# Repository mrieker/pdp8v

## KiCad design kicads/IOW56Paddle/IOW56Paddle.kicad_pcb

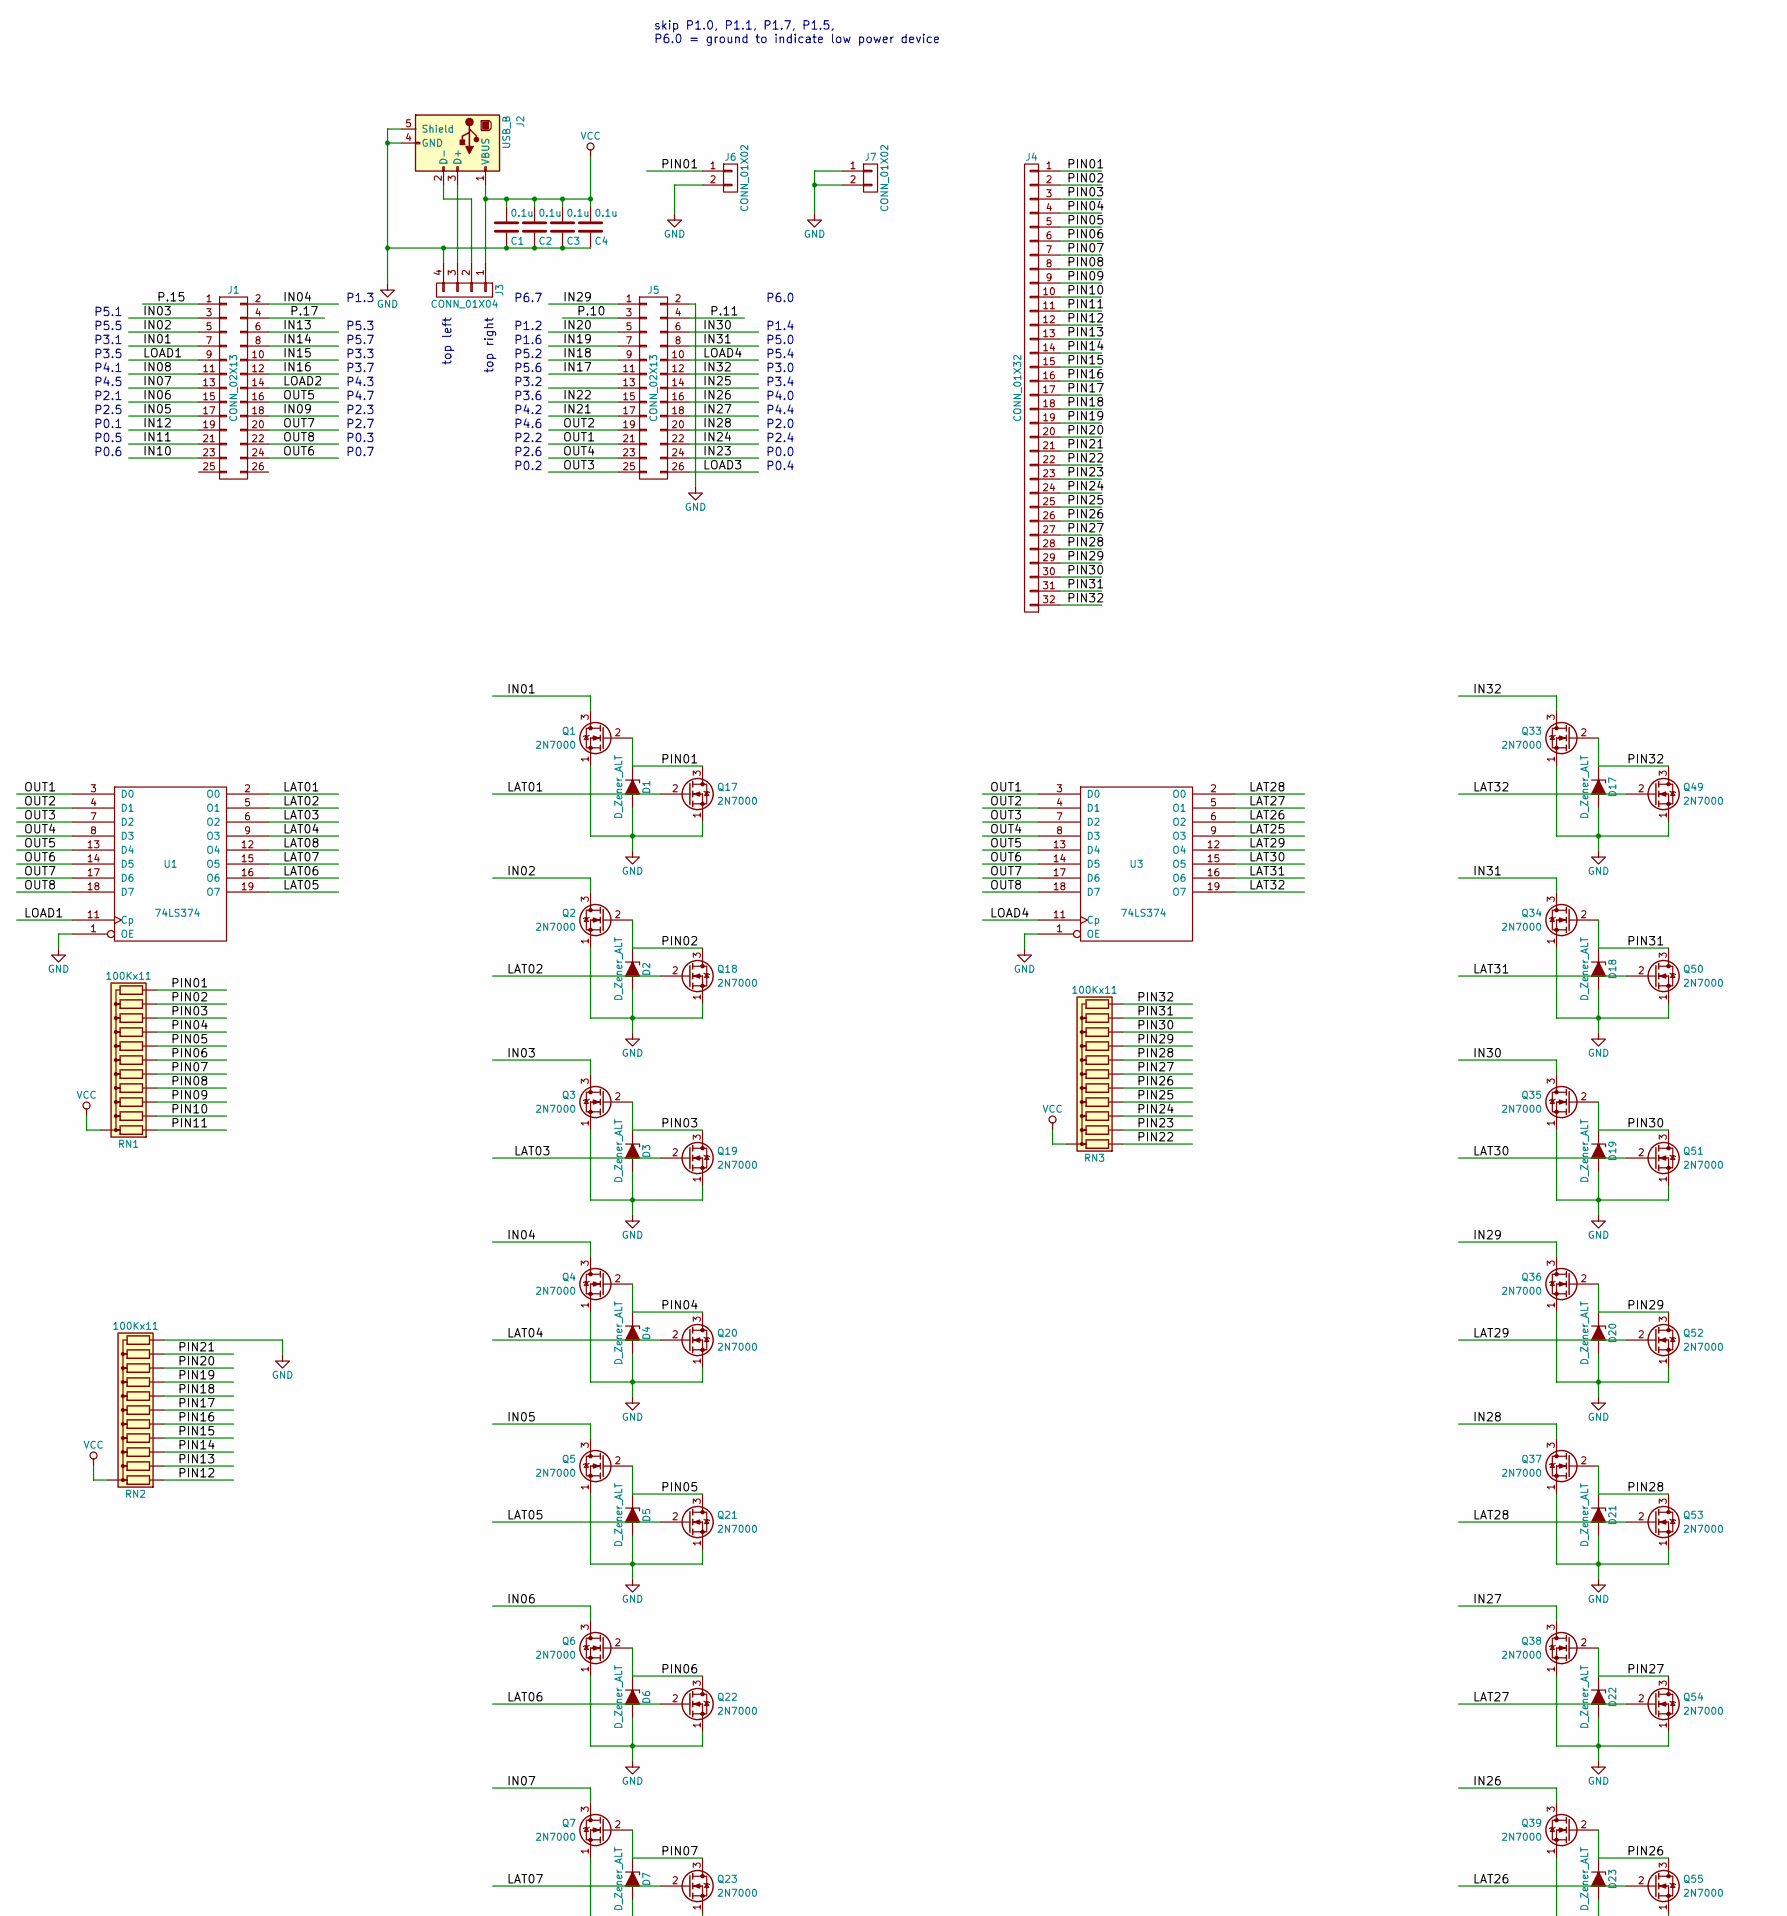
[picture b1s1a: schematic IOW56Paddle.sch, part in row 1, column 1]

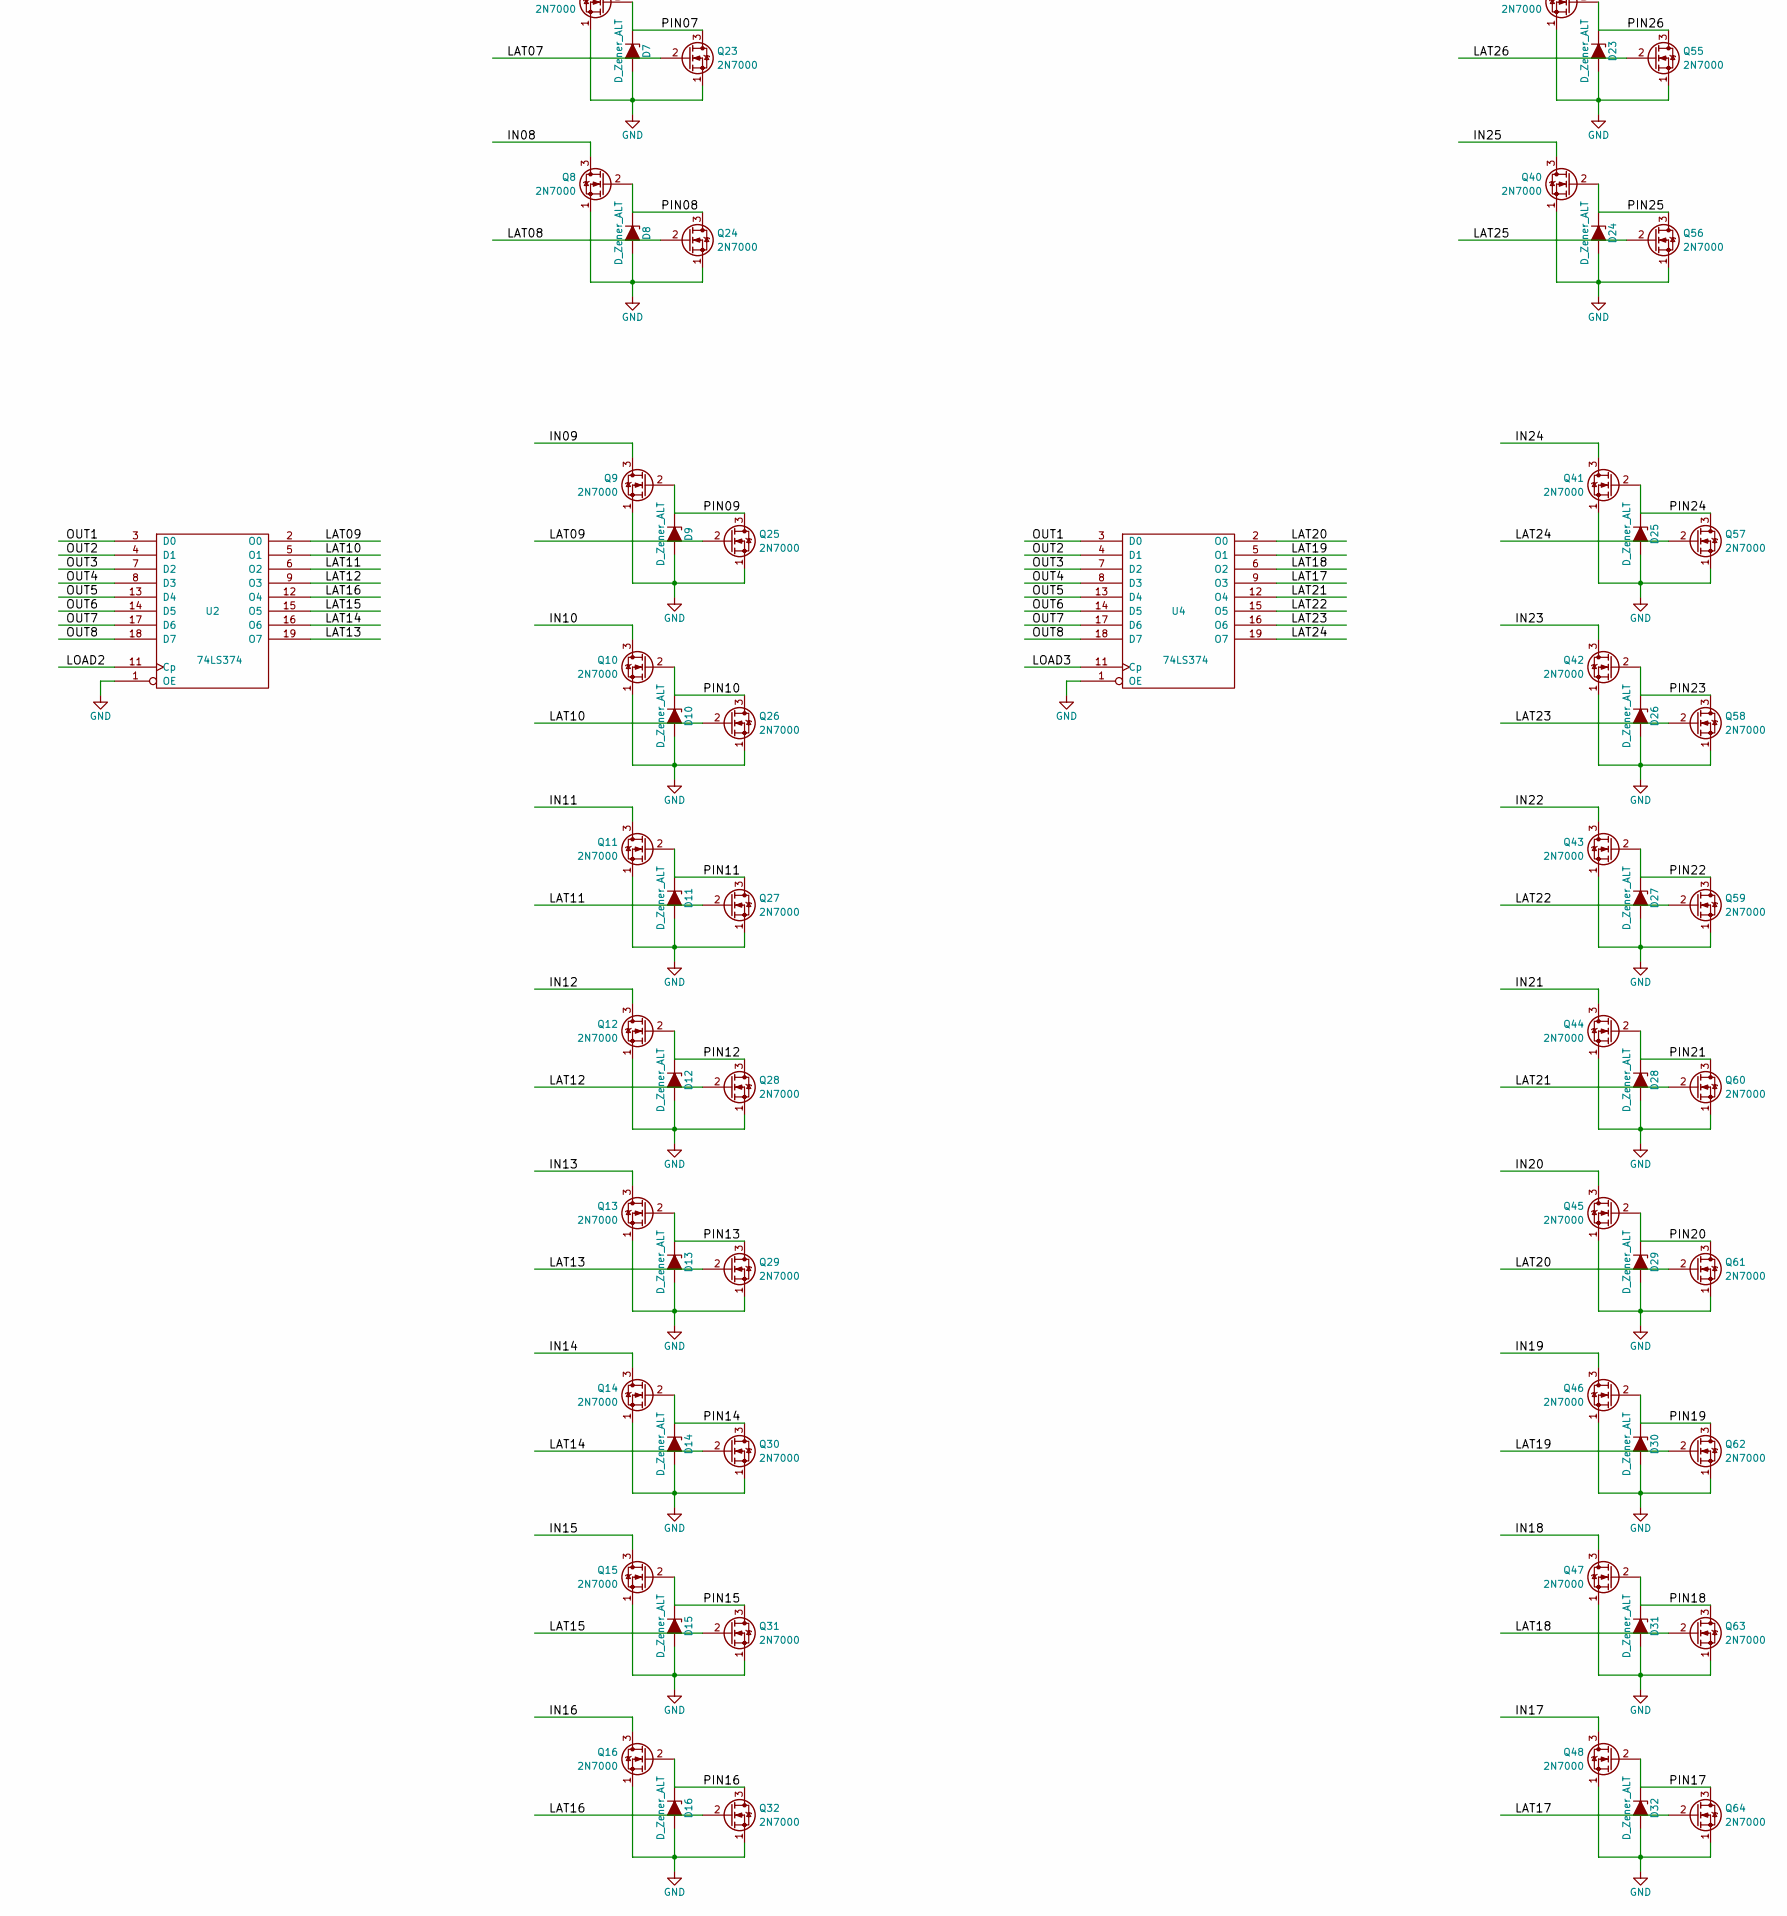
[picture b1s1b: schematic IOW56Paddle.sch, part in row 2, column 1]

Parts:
C1, C2, C3, C4: 0.1u; C_Axial_L5.1mm_D3.1mm_P7.50mm_Horizontal
D1, D2, D3, D4, D5, D6, D7, D8, D9, D10, D11, D12, D13, D14, D15, D16, D17, D18, D19, D20, D21, D22, D23, D24, D25, D26, D27, D28, D29, D30, D31, D32: D_Zener_ALT; D_DO-35_SOD27_P6.35mm_Horizontal
J1, J5: CONN_02X13; Pin_Header_Straight_2x13_Pitch2.54mm
J2: USB_B
J3: CONN_01X04; Pin_Header_Straight_1x04_Pitch2.54mm
J4: CONN_01X32; Pin_Header_Straight_1x32_Pitch2.54mm
J6, J7: CONN_01X02; Pin_Header_Straight_1x02_Pitch2.54mm
Q1, Q2, Q3, Q4, Q5, Q6, Q7, Q8, Q9, Q10, Q11, Q12, Q13, Q14, Q15, Q16, Q17, Q18, Q19, Q20, Q21, Q22, Q23, Q24, Q25, Q26, Q27, Q28, Q29, Q30, Q31, Q32, Q33, Q34, Q35, Q36, Q37, Q38, Q39, Q40, Q41, Q42, Q43, Q44, Q45, Q46, Q47, Q48, Q49, Q50, Q51, Q52, Q53, Q54, Q55, Q56, Q57, Q58, Q59, Q60, Q61, Q62, Q63, Q64: 2N7000; TO-92_Molded_Wide
RN1, RN2, RN3: 100Kx11; R_Array_SIP12
U1, U2, U3, U4: 74LS374; DIP-20_W7.62mm

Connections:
/IN01: J1.7, Q1.3 (D)
/IN02: J1.5, Q2.3 (D)
/IN03: J1.3, Q3.3 (D)
/IN04: J1.2, Q4.3 (D)
/IN05: J1.17, Q5.3 (D)
/IN06: J1.15, Q6.3 (D)
/IN07: J1.13, Q7.3 (D)
/IN08: J1.11, Q8.3 (D)
/IN09: J1.18, Q9.3 (D)
/IN10: J1.23, Q10.3 (D)
/IN11: J1.21, Q11.3 (D)
/IN12: J1.19, Q12.3 (D)
/IN13: J1.6, Q13.3 (D)
/IN14: J1.8, Q14.3 (D)
/IN15: J1.10, Q15.3 (D)
/IN16: J1.12, Q16.3 (D)
/IN17: J5.11, Q48.3 (D)
/IN18: J5.9, Q47.3 (D)
/IN19: J5.7, Q46.3 (D)
/IN20: J5.5, Q45.3 (D)
/IN21: J5.17, Q44.3 (D)
/IN22: J5.15, Q43.3 (D)
/IN23: J5.24, Q42.3 (D)
/IN24: J5.22, Q41.3 (D)
/IN25: J5.14, Q40.3 (D)
/IN26: J5.16, Q39.3 (D)
/IN27: J5.18, Q38.3 (D)
/IN28: J5.20, Q37.3 (D)
/IN29: J5.1, Q36.3 (D)
/IN30: J5.6, Q35.3 (D)
/IN31: J5.8, Q34.3 (D)
/IN32: J5.12, Q33.3 (D)
/LAT01: Q17.2 (G), U1.2 (O0)
/LAT02: Q18.2 (G), U1.5 (O1)
/LAT03: Q19.2 (G), U1.6 (O2)
/LAT04: Q20.2 (G), U1.9 (O3)
/LAT05: Q21.2 (G), U1.19 (O7)
/LAT06: Q22.2 (G), U1.16 (O6)
/LAT07: Q23.2 (G), U1.15 (O5)
/LAT08: Q24.2 (G), U1.12 (O4)
/LAT09: Q25.2 (G), U2.2 (O0)
/LAT10: Q26.2 (G), U2.5 (O1)
/LAT11: Q27.2 (G), U2.6 (O2)
/LAT12: Q28.2 (G), U2.9 (O3)
/LAT13: Q29.2 (G), U2.19 (O7)
/LAT14: Q30.2 (G), U2.16 (O6)
/LAT15: Q31.2 (G), U2.15 (O5)
/LAT16: Q32.2 (G), U2.12 (O4)
/LAT17: Q64.2 (G), U4.9 (O3)
/LAT18: Q63.2 (G), U4.6 (O2)
/LAT19: Q62.2 (G), U4.5 (O1)
/LAT20: Q61.2 (G), U4.2 (O0)
/LAT21: Q60.2 (G), U4.12 (O4)
/LAT22: Q59.2 (G), U4.15 (O5)
/LAT23: Q58.2 (G), U4.16 (O6)
/LAT24: Q57.2 (G), U4.19 (O7)
/LAT25: Q56.2 (G), U3.9 (O3)
/LAT26: Q55.2 (G), U3.6 (O2)
/LAT27: Q54.2 (G), U3.5 (O1)
/LAT28: Q53.2 (G), U3.2 (O0)
/LAT29: Q52.2 (G), U3.12 (O4)
/LAT30: Q51.2 (G), U3.15 (O5)
/LAT31: Q50.2 (G), U3.16 (O6)
/LAT32: Q49.2 (G), U3.19 (O7)
/LOAD1: J1.9, U1.11 (Cp)
/LOAD2: J1.14, U2.11 (Cp)
/LOAD3: J5.26, U4.11 (Cp)
/LOAD4: J5.10, U3.11 (Cp)
/OUT1: J5.21, U1.3 (D0), U2.3 (D0), U3.3 (D0), U4.3 (D0)
/OUT2: J5.19, U1.4 (D1), U2.4 (D1), U3.4 (D1), U4.4 (D1)
/OUT3: J5.25, U1.7 (D2), U2.7 (D2), U3.7 (D2), U4.7 (D2)
/OUT4: J5.23, U1.8 (D3), U2.8 (D3), U3.8 (D3), U4.8 (D3)
/OUT5: J1.16, U1.13 (D4), U2.13 (D4), U3.13 (D4), U4.13 (D4)
/OUT6: J1.24, U1.14 (D5), U2.14 (D5), U3.14 (D5), U4.14 (D5)
/OUT7: J1.20, U1.17 (D6), U2.17 (D6), U3.17 (D6), U4.17 (D6)
/OUT8: J1.22, U1.18 (D7), U2.18 (D7), U3.18 (D7), U4.18 (D7)
/P.10: J5.3
/P.11: J5.4
/P.15: J1.1
/P.17: J1.4
/PIN01: D1.1 (K), J4.1, J6.1, Q1.2 (G), Q17.3 (D), RN1.12 (R11)
/PIN02: D2.1 (K), J4.2, Q2.2 (G), Q18.3 (D), RN1.11 (R10)
/PIN03: D3.1 (K), J4.3, Q3.2 (G), Q19.3 (D), RN1.10 (R9)
/PIN04: D4.1 (K), J4.4, Q4.2 (G), Q20.3 (D), RN1.9 (R8)
/PIN05: D5.1 (K), J4.5, Q5.2 (G), Q21.3 (D), RN1.8 (R7)
/PIN06: D6.1 (K), J4.6, Q6.2 (G), Q22.3 (D), RN1.7 (R6)
/PIN07: D7.1 (K), J4.7, Q7.2 (G), Q23.3 (D), RN1.6 (R5)
/PIN08: D8.1 (K), J4.8, Q8.2 (G), Q24.3 (D), RN1.5 (R4)
/PIN09: D9.1 (K), J4.9, Q9.2 (G), Q25.3 (D), RN1.4 (R3)
/PIN10: D10.1 (K), J4.10, Q10.2 (G), Q26.3 (D), RN1.3 (R2)
/PIN11: D11.1 (K), J4.11, Q11.2 (G), Q27.3 (D), RN1.2 (R1)
/PIN12: D12.1 (K), J4.12, Q12.2 (G), Q28.3 (D), RN2.2 (R1)
/PIN13: D13.1 (K), J4.13, Q13.2 (G), Q29.3 (D), RN2.3 (R2)
/PIN14: D14.1 (K), J4.14, Q14.2 (G), Q30.3 (D), RN2.4 (R3)
/PIN15: D15.1 (K), J4.15, Q15.2 (G), Q31.3 (D), RN2.5 (R4)
/PIN16: D16.1 (K), J4.16, Q16.2 (G), Q32.3 (D), RN2.6 (R5)
/PIN17: D32.1 (K), J4.17, Q48.2 (G), Q64.3 (D), RN2.7 (R6)
/PIN18: D31.1 (K), J4.18, Q47.2 (G), Q63.3 (D), RN2.8 (R7)
/PIN19: D30.1 (K), J4.19, Q46.2 (G), Q62.3 (D), RN2.9 (R8)
/PIN20: D29.1 (K), J4.20, Q45.2 (G), Q61.3 (D), RN2.10 (R9)
/PIN21: D28.1 (K), J4.21, Q44.2 (G), Q60.3 (D), RN2.11 (R10)
/PIN22: D27.1 (K), J4.22, Q43.2 (G), Q59.3 (D), RN3.2 (R1)
/PIN23: D26.1 (K), J4.23, Q42.2 (G), Q58.3 (D), RN3.3 (R2)
/PIN24: D25.1 (K), J4.24, Q41.2 (G), Q57.3 (D), RN3.4 (R3)
/PIN25: D24.1 (K), J4.25, Q40.2 (G), Q56.3 (D), RN3.5 (R4)
/PIN26: D23.1 (K), J4.26, Q39.2 (G), Q55.3 (D), RN3.6 (R5)
/PIN27: D22.1 (K), J4.27, Q38.2 (G), Q54.3 (D), RN3.7 (R6)
/PIN28: D21.1 (K), J4.28, Q37.2 (G), Q53.3 (D), RN3.8 (R7)
/PIN29: D20.1 (K), J4.29, Q36.2 (G), Q52.3 (D), RN3.9 (R8)
/PIN30: D19.1 (K), J4.30, Q35.2 (G), Q51.3 (D), RN3.10 (R9)
/PIN31: D18.1 (K), J4.31, Q34.2 (G), Q50.3 (D), RN3.11 (R10)
/PIN32: D17.1 (K), J4.32, Q33.2 (G), Q49.3 (D), RN3.12 (R11)
GND: C1.1, C2.1, C3.1, C4.1, D1.2 (A), D2.2 (A), D3.2 (A), D4.2 (A), D5.2 (A), D6.2 (A), D7.2 (A), D8.2 (A), D9.2 (A), D10.2 (A), D11.2 (A), D12.2 (A), D13.2 (A), D14.2 (A), D15.2 (A), D16.2 (A), D17.2 (A), D18.2 (A), D19.2 (A), D20.2 (A), D21.2 (A), D22.2 (A), D23.2 (A), D24.2 (A), D25.2 (A), D26.2 (A), D27.2 (A), D28.2 (A), D29.2 (A), D30.2 (A), D31.2 (A), D32.2 (A), J2.4 (GND), J2.5 (Shield), J3.4, J5.2, J6.2, J7.1, J7.2, Q1.1 (S), Q2.1 (S), Q3.1 (S), Q4.1 (S), Q5.1 (S), Q6.1 (S), Q7.1 (S), Q8.1 (S), Q9.1 (S), Q10.1 (S), Q11.1 (S), Q12.1 (S), Q13.1 (S), Q14.1 (S), Q15.1 (S), Q16.1 (S), Q17.1 (S), Q18.1 (S), Q19.1 (S), Q20.1 (S), Q21.1 (S), Q22.1 (S), Q23.1 (S), Q24.1 (S), Q25.1 (S), Q26.1 (S), Q27.1 (S), Q28.1 (S), Q29.1 (S), Q30.1 (S), Q31.1 (S), Q32.1 (S), Q33.1 (S), Q34.1 (S), Q35.1 (S), Q36.1 (S), Q37.1 (S), Q38.1 (S), Q39.1 (S), Q40.1 (S), Q41.1 (S), Q42.1 (S), Q43.1 (S), Q44.1 (S), Q45.1 (S), Q46.1 (S), Q47.1 (S), Q48.1 (S), Q49.1 (S), Q50.1 (S), Q51.1 (S), Q52.1 (S), Q53.1 (S), Q54.1 (S), Q55.1 (S), Q56.1 (S), Q57.1 (S), Q58.1 (S), Q59.1 (S), Q60.1 (S), Q61.1 (S), Q62.1 (S), Q63.1 (S), Q64.1 (S), RN2.12 (R11), U1.1 (OE), U1.10 (GND), U2.1 (OE), U2.10 (GND), U3.1 (OE), U3.10 (GND), U4.1 (OE), U4.10 (GND)
unnamed: J2.2 (D-), J3.2
unnamed: J2.3 (D+), J3.3
VCC: C1.2, C2.2, C3.2, C4.2, J2.1 (VBUS), J3.1, RN1.1 (common), RN2.1 (common), RN3.1 (common), U1.20 (VCC), U2.20 (VCC), U3.20 (VCC), U4.20 (VCC)

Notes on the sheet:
top right
top left
skip P1.0, P1.1, P1.7, P1.5, P6.0 = ground to indicate low power device
P5.1
P5.5
P3.1
P3.5
P4.1
P4.5
P2.1
P2.5
P0.1
P0.5
P0.6
P1.3
P5.3
P5.7
P3.3
P3.7
P4.3
P4.7
P2.3
P2.7
P0.3
P0.7
P6.7
P1.2
P1.6
P5.2
P5.6
P3.2
P3.6
P4.2
P4.6
P2.2
P2.6
P0.2
P6.0
P1.4
P5.0

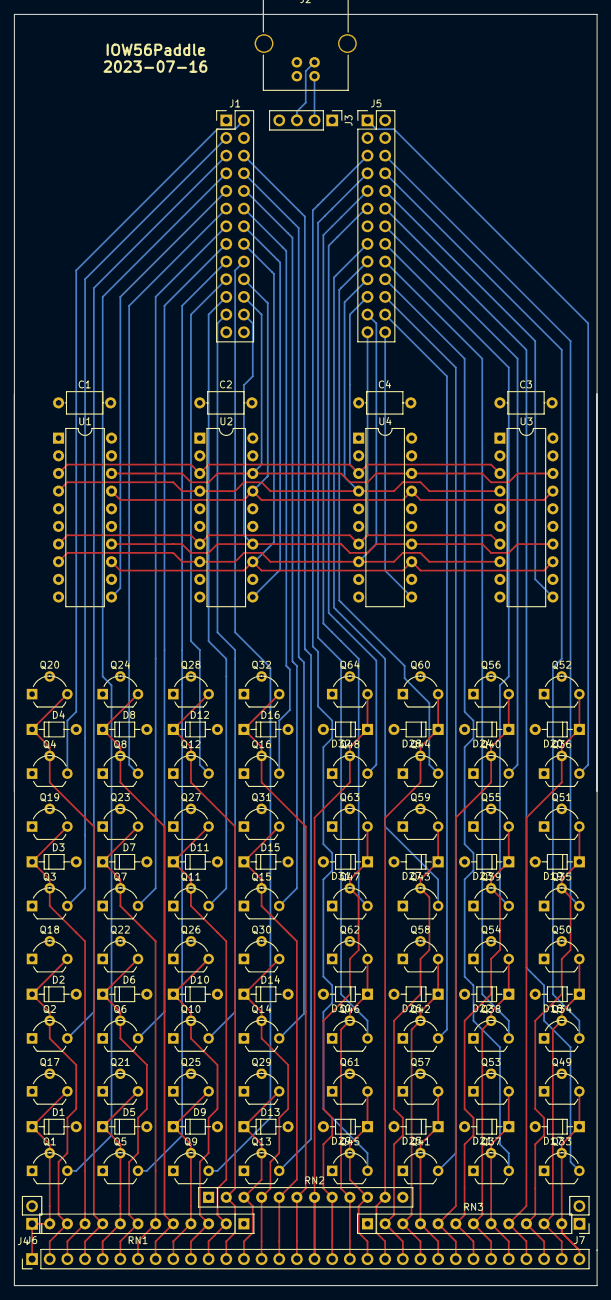
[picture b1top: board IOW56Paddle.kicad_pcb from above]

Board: 4 copper layers, 83.8 x 182.9 mm, 114 parts (0 on the bottom side), 112 nets.

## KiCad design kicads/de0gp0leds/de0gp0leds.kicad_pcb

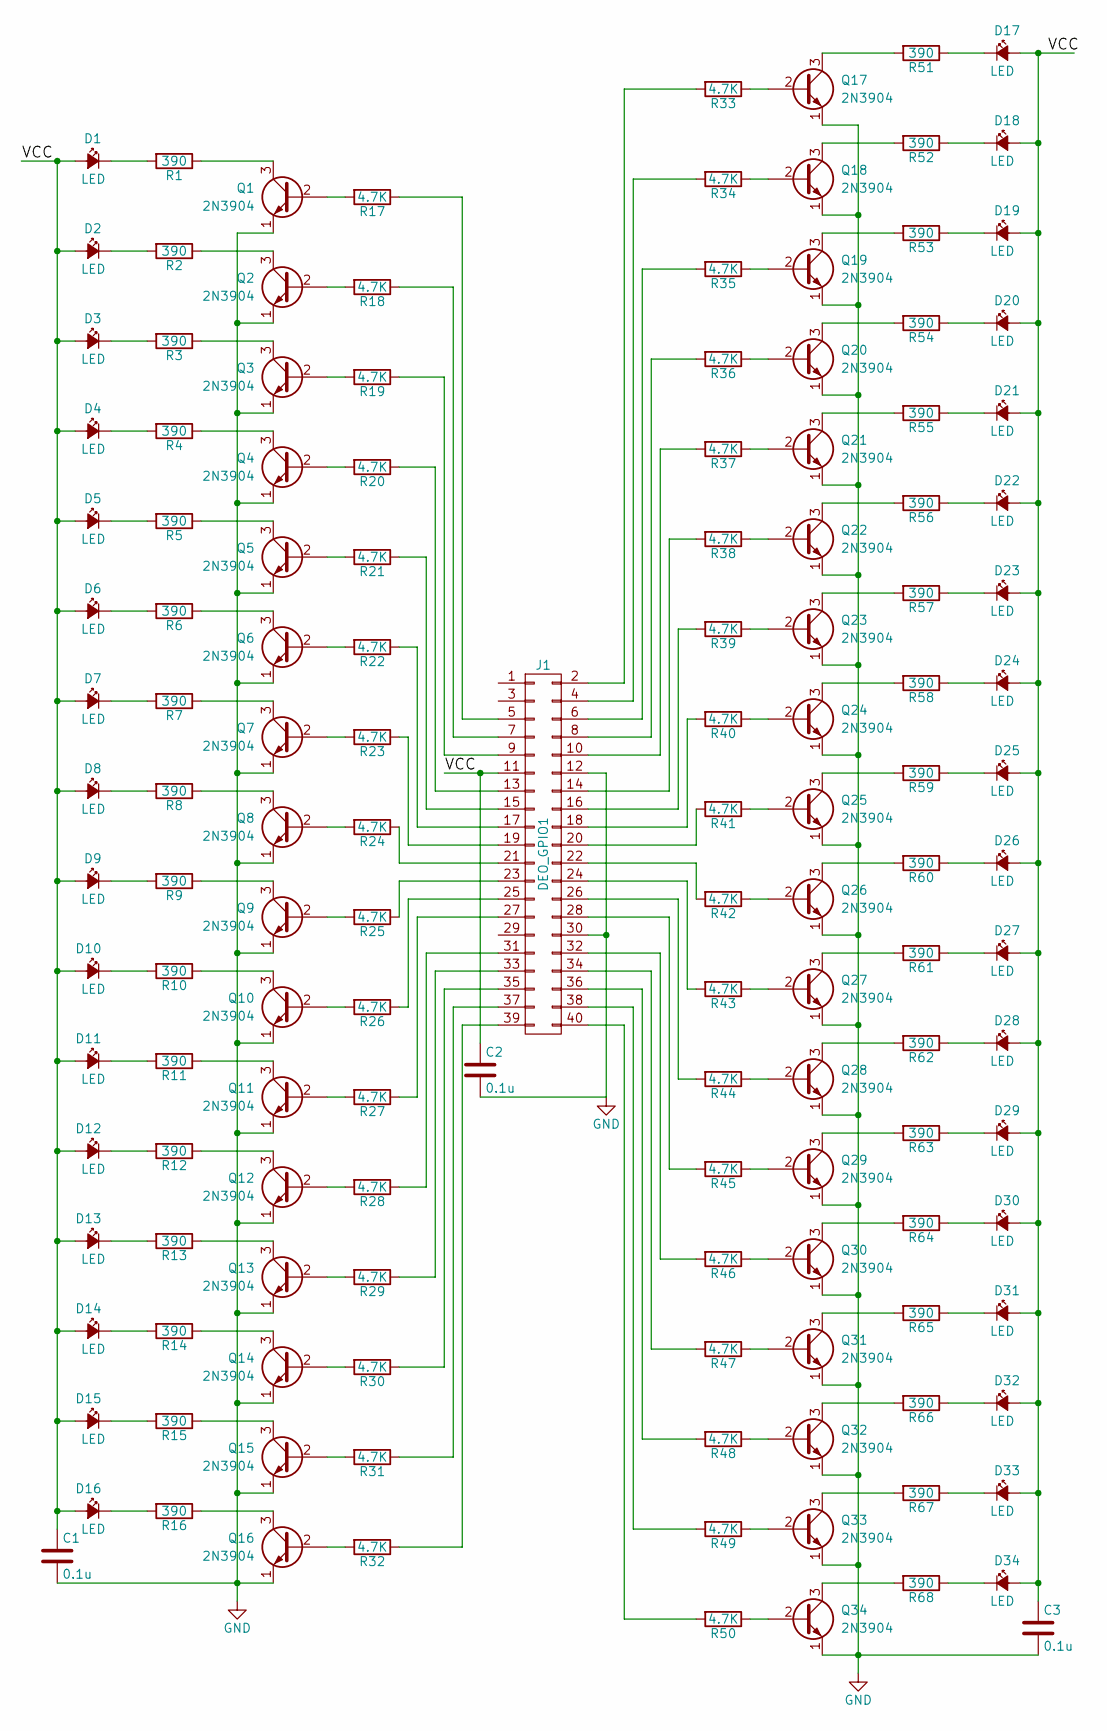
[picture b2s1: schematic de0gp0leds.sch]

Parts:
C1, C2, C3: 0.1u; R_Axial_DIN0204_L3.6mm_D1.6mm_P5.08mm_Horizontal
D1, D2, D3, D4, D5, D6, D7, D8, D9, D10, D11, D12, D13, D14, D15, D16, D17, D18, D19, D20, D21, D22, D23, D24, D25, D26, D27, D28, D29, D30, D31, D32, D33, D34: LED; LED_D3.0mm
J1: DEO_GPIO1; Pin_Header_Straight_2x20_Pitch2.54mm
Q1, Q2, Q3, Q4, Q5, Q6, Q7, Q8, Q9, Q10, Q11, Q12, Q13, Q14, Q15, Q16, Q17, Q18, Q19, Q20, Q21, Q22, Q23, Q24, Q25, Q26, Q27, Q28, Q29, Q30, Q31, Q32, Q33, Q34: 2N3904; TO-92_Molded_Wide
R1, R2, R3, R4, R5, R6, R7, R8, R9, R10, R11, R12, R13, R14, R15, R16, R51, R52, R53, R54, R55, R56, R57, R58, R59, R60, R61, R62, R63, R64, R65, R66, R67, R68: 390; R_Axial_DIN0204_L3.6mm_D1.6mm_P5.08mm_Horizontal
R17, R18, R19, R20, R21, R22, R23, R24, R25, R26, R27, R28, R29, R30, R31, R32, R33, R34, R35, R36, R37, R38, R39, R40, R41, R42, R43, R44, R45, R46, R47, R48, R49, R50: 4.7K; R_Axial_DIN0204_L3.6mm_D1.6mm_P5.08mm_Horizontal

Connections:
/VCC: C1.1, C2.1, C3.1, D1.2 (A), D2.2 (A), D3.2 (A), D4.2 (A), D5.2 (A), D6.2 (A), D7.2 (A), D8.2 (A), D9.2 (A), D10.2 (A), D11.2 (A), D12.2 (A), D13.2 (A), D14.2 (A), D15.2 (A), D16.2 (A), D17.2 (A), D18.2 (A), D19.2 (A), D20.2 (A), D21.2 (A), D22.2 (A), D23.2 (A), D24.2 (A), D25.2 (A), D26.2 (A), D27.2 (A), D28.2 (A), D29.2 (A), D30.2 (A), D31.2 (A), D32.2 (A), D33.2 (A), D34.2 (A), J1.11
GND: C1.2, C2.2, C3.2, J1.12, J1.30, Q1.1 (E), Q2.1 (E), Q3.1 (E), Q4.1 (E), Q5.1 (E), Q6.1 (E), Q7.1 (E), Q8.1 (E), Q9.1 (E), Q10.1 (E), Q11.1 (E), Q12.1 (E), Q13.1 (E), Q14.1 (E), Q15.1 (E), Q16.1 (E), Q17.1 (E), Q18.1 (E), Q19.1 (E), Q20.1 (E), Q21.1 (E), Q22.1 (E), Q23.1 (E), Q24.1 (E), Q25.1 (E), Q26.1 (E), Q27.1 (E), Q28.1 (E), Q29.1 (E), Q30.1 (E), Q31.1 (E), Q32.1 (E), Q33.1 (E), Q34.1 (E)
unnamed: D1.1 (K), R1.2
unnamed: D2.1 (K), R2.2
unnamed: D3.1 (K), R3.2
unnamed: D4.1 (K), R4.2
unnamed: D5.1 (K), R5.2
unnamed: D6.1 (K), R6.2
unnamed: D7.1 (K), R7.2
unnamed: D8.1 (K), R8.2
unnamed: D9.1 (K), R9.2
unnamed: D10.1 (K), R10.2
unnamed: D11.1 (K), R11.2
unnamed: D12.1 (K), R12.2
unnamed: D13.1 (K), R13.2
unnamed: D14.1 (K), R14.2
unnamed: D15.1 (K), R15.2
unnamed: D16.1 (K), R16.2
unnamed: D17.1 (K), R51.1
unnamed: D18.1 (K), R52.1
unnamed: D19.1 (K), R53.1
unnamed: D20.1 (K), R54.1
unnamed: D21.1 (K), R55.1
unnamed: D22.1 (K), R56.1
unnamed: D23.1 (K), R57.1
unnamed: D24.1 (K), R58.1
unnamed: D25.1 (K), R59.1
unnamed: D26.1 (K), R60.1
unnamed: D27.1 (K), R61.1
unnamed: D28.1 (K), R62.1
unnamed: D29.1 (K), R63.1
unnamed: D30.1 (K), R64.1
unnamed: D31.1 (K), R65.1
unnamed: D32.1 (K), R66.1
unnamed: D33.1 (K), R67.1
unnamed: D34.1 (K), R68.1
unnamed: J1.2, R33.2
unnamed: J1.4, R34.2
unnamed: J1.5, R17.1
unnamed: J1.6, R35.2
unnamed: J1.7, R18.1
unnamed: J1.8, R36.2
unnamed: J1.9, R19.1
unnamed: J1.10, R37.2
unnamed: J1.13, R20.1
unnamed: J1.14, R38.2
unnamed: J1.15, R21.1
unnamed: J1.16, R39.2
unnamed: J1.17, R22.1
unnamed: J1.18, R40.2
unnamed: J1.19, R23.1
unnamed: J1.20, R41.2
unnamed: J1.21, R24.1
unnamed: J1.22, R42.2
unnamed: J1.23, R25.1
unnamed: J1.24, R43.2
unnamed: J1.25, R26.1
unnamed: J1.26, R44.2
unnamed: J1.27, R27.1
unnamed: J1.28, R45.2
unnamed: J1.31, R28.1
unnamed: J1.32, R46.2
unnamed: J1.33, R29.1
unnamed: J1.34, R47.2
unnamed: J1.35, R30.1
unnamed: J1.36, R48.2
unnamed: J1.37, R31.1
unnamed: J1.38, R49.2
unnamed: J1.39, R32.1
unnamed: J1.40, R50.2
unnamed: Q1.2 (B), R17.2
unnamed: Q1.3 (C), R1.1
unnamed: Q2.2 (B), R18.2
unnamed: Q2.3 (C), R2.1
unnamed: Q3.2 (B), R19.2
unnamed: Q3.3 (C), R3.1
unnamed: Q4.2 (B), R20.2
unnamed: Q4.3 (C), R4.1
unnamed: Q5.2 (B), R21.2
unnamed: Q5.3 (C), R5.1
unnamed: Q6.2 (B), R22.2
unnamed: Q6.3 (C), R6.1
unnamed: Q7.2 (B), R23.2
unnamed: Q7.3 (C), R7.1
unnamed: Q8.2 (B), R24.2
unnamed: Q8.3 (C), R8.1
unnamed: Q9.2 (B), R25.2
unnamed: Q9.3 (C), R9.1
unnamed: Q10.2 (B), R26.2
unnamed: Q10.3 (C), R10.1
unnamed: Q11.2 (B), R27.2
unnamed: Q11.3 (C), R11.1
unnamed: Q12.2 (B), R28.2
unnamed: Q12.3 (C), R12.1
unnamed: Q13.2 (B), R29.2
unnamed: Q13.3 (C), R13.1
unnamed: Q14.2 (B), R30.2
unnamed: Q14.3 (C), R14.1
unnamed: Q15.2 (B), R31.2
unnamed: Q15.3 (C), R15.1
unnamed: Q16.2 (B), R32.2
unnamed: Q16.3 (C), R16.1
unnamed: Q17.2 (B), R33.1
unnamed: Q17.3 (C), R51.2
unnamed: Q18.2 (B), R34.1
unnamed: Q18.3 (C), R52.2
unnamed: Q19.2 (B), R35.1
unnamed: Q19.3 (C), R53.2
unnamed: Q20.2 (B), R36.1
unnamed: Q20.3 (C), R54.2
unnamed: Q21.2 (B), R37.1
unnamed: Q21.3 (C), R55.2
unnamed: Q22.2 (B), R38.1
unnamed: Q22.3 (C), R56.2
unnamed: Q23.2 (B), R39.1
unnamed: Q23.3 (C), R57.2
unnamed: Q24.2 (B), R40.1
unnamed: Q24.3 (C), R58.2
unnamed: Q25.2 (B), R41.1
unnamed: Q25.3 (C), R59.2
unnamed: Q26.2 (B), R42.1
unnamed: Q26.3 (C), R60.2
unnamed: Q27.2 (B), R43.1
unnamed: Q27.3 (C), R61.2
unnamed: Q28.2 (B), R44.1
unnamed: Q28.3 (C), R62.2
unnamed: Q29.2 (B), R45.1
unnamed: Q29.3 (C), R63.2
unnamed: Q30.2 (B), R46.1
unnamed: Q30.3 (C), R64.2
unnamed: Q31.2 (B), R47.1
unnamed: Q31.3 (C), R65.2
unnamed: Q32.2 (B), R48.1
unnamed: Q32.3 (C), R66.2
unnamed: Q33.2 (B), R49.1
unnamed: Q33.3 (C), R67.2
unnamed: Q34.2 (B), R50.1
unnamed: Q34.3 (C), R68.2

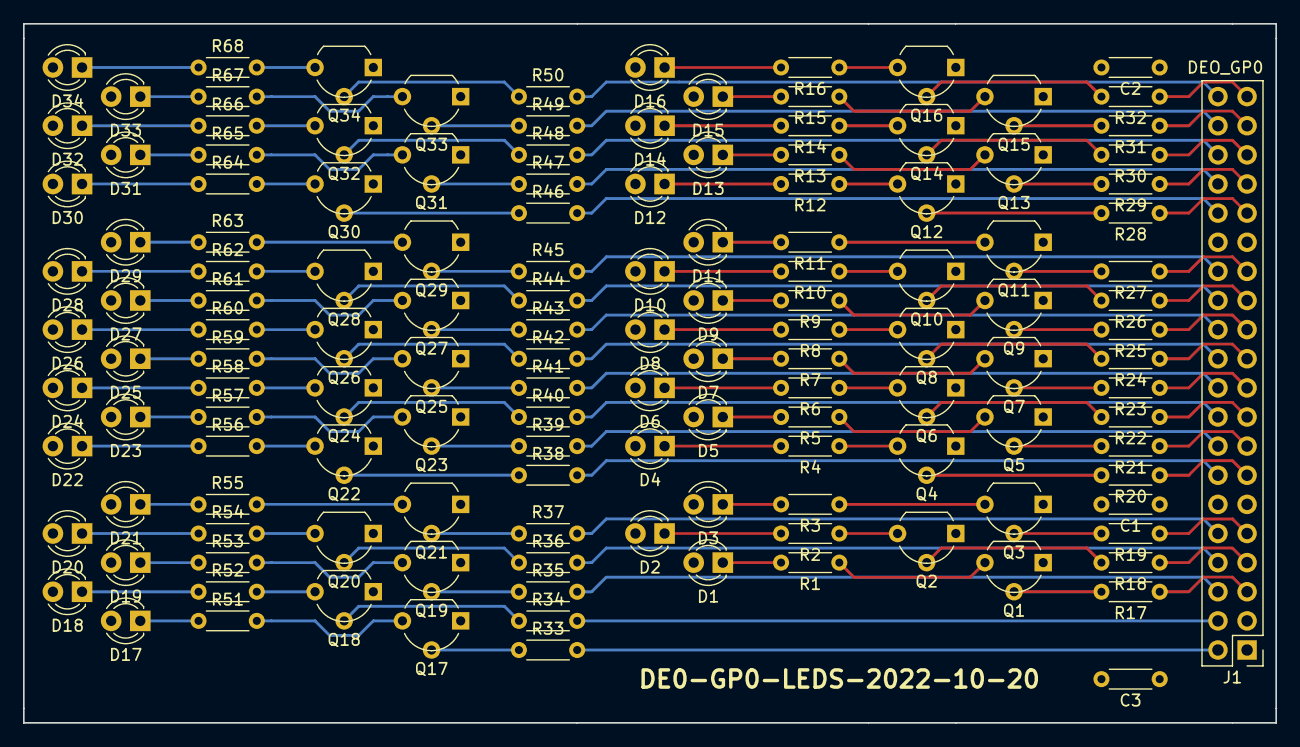
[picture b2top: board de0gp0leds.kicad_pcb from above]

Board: 4 copper layers, 109.2 x 61.0 mm, 140 parts (0 on the bottom side), 138 nets.

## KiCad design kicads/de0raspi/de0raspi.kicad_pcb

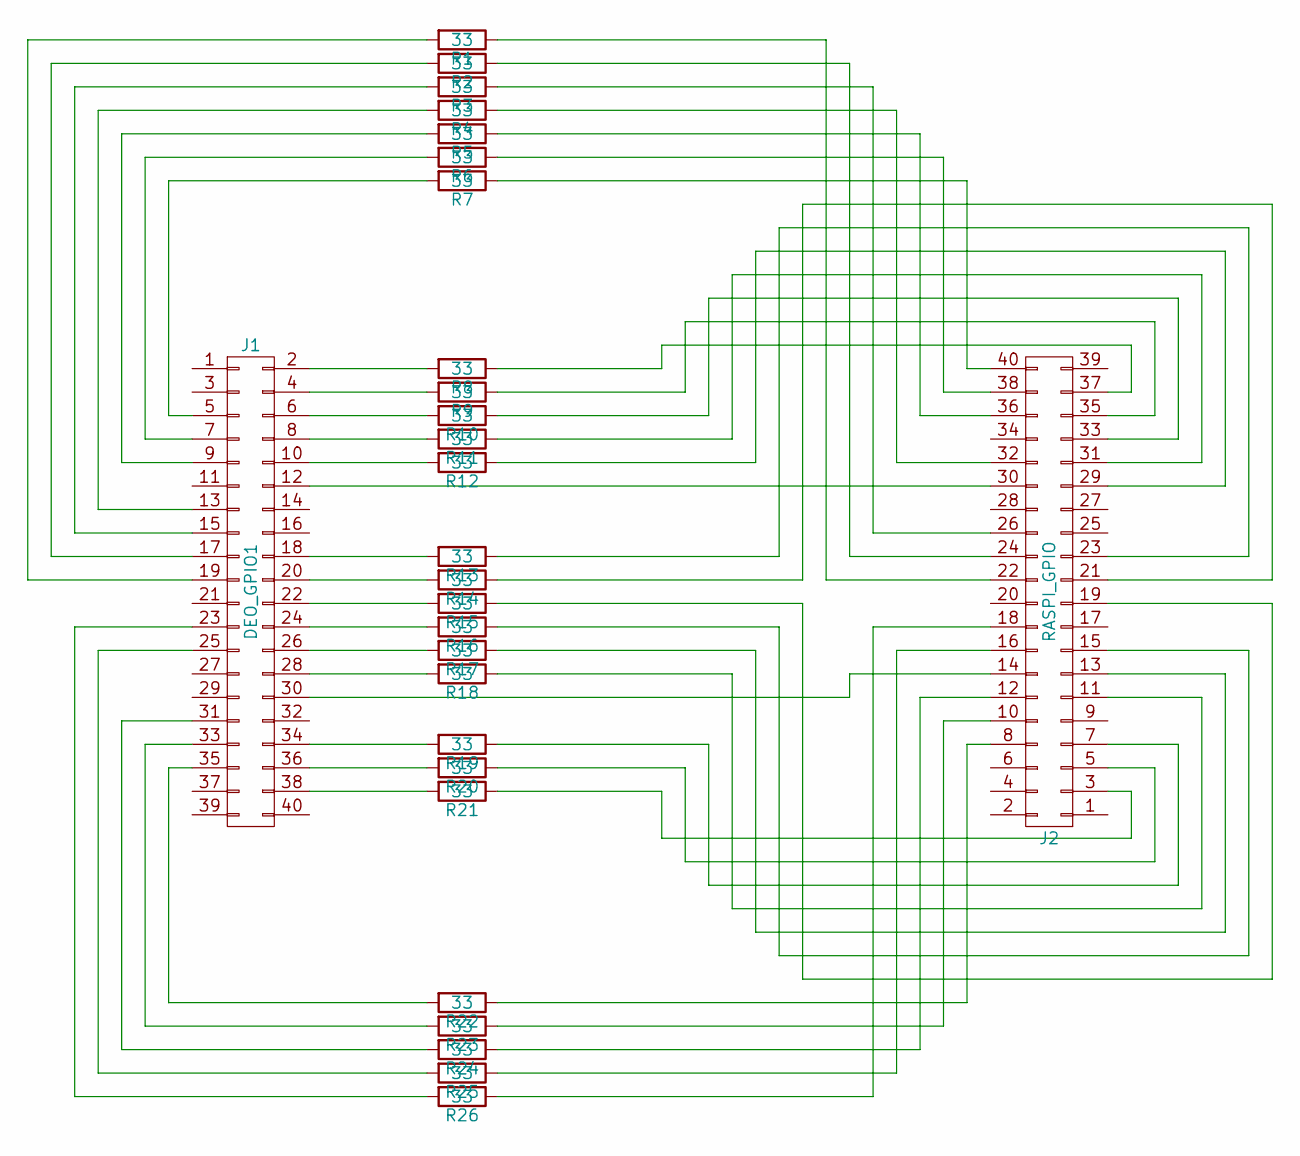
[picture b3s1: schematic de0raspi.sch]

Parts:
J1: DEO_GPIO1; Pin_Header_Straight_2x20_Pitch2.54mm
J2: RASPI_GPIO; Pin_Header_Straight_2x20_Pitch2.54mm
R1, R2, R3, R4, R5, R6, R7, R8, R9, R10, R11, R12, R13, R14, R15, R16, R17, R18, R19, R20, R21, R22, R23, R24, R25, R26: 33; R_Axial_DIN0204_L3.6mm_D1.6mm_P5.08mm_Horizontal

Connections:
unnamed: J1.2, R8.2
unnamed: J1.4, R9.2
unnamed: J1.5, R7.2
unnamed: J1.6, R10.2
unnamed: J1.7, R6.2
unnamed: J1.8, R11.2
unnamed: J1.9, R5.2
unnamed: J1.10, R12.2
unnamed: J1.12, J2.30
unnamed: J1.13, R4.2
unnamed: J1.15, R3.2
unnamed: J1.17, R2.2
unnamed: J1.18, R13.2
unnamed: J1.19, R1.2
unnamed: J1.20, R14.2
unnamed: J1.22, R15.2
unnamed: J1.23, R26.2
unnamed: J1.24, R16.2
unnamed: J1.25, R25.2
unnamed: J1.26, R17.2
unnamed: J1.28, R18.2
unnamed: J1.30, J2.14
unnamed: J1.31, R24.2
unnamed: J1.33, R23.2
unnamed: J1.34, R19.2
unnamed: J1.35, R22.2
unnamed: J1.36, R20.2
unnamed: J1.38, R21.2
unnamed: J2.3, R21.1
unnamed: J2.5, R20.1
unnamed: J2.7, R19.1
unnamed: J2.8, R22.1
unnamed: J2.10, R23.1
unnamed: J2.11, R18.1
unnamed: J2.12, R24.1
unnamed: J2.13, R17.1
unnamed: J2.15, R16.1
unnamed: J2.16, R25.1
unnamed: J2.18, R26.1
unnamed: J2.19, R15.1
unnamed: J2.21, R14.1
unnamed: J2.22, R1.1
unnamed: J2.23, R13.1
unnamed: J2.24, R2.1
unnamed: J2.26, R3.1
unnamed: J2.29, R12.1
unnamed: J2.31, R11.1
unnamed: J2.32, R4.1
unnamed: J2.33, R10.1
unnamed: J2.35, R9.1
unnamed: J2.36, R5.1
unnamed: J2.37, R8.1
unnamed: J2.38, R6.1
unnamed: J2.40, R7.1

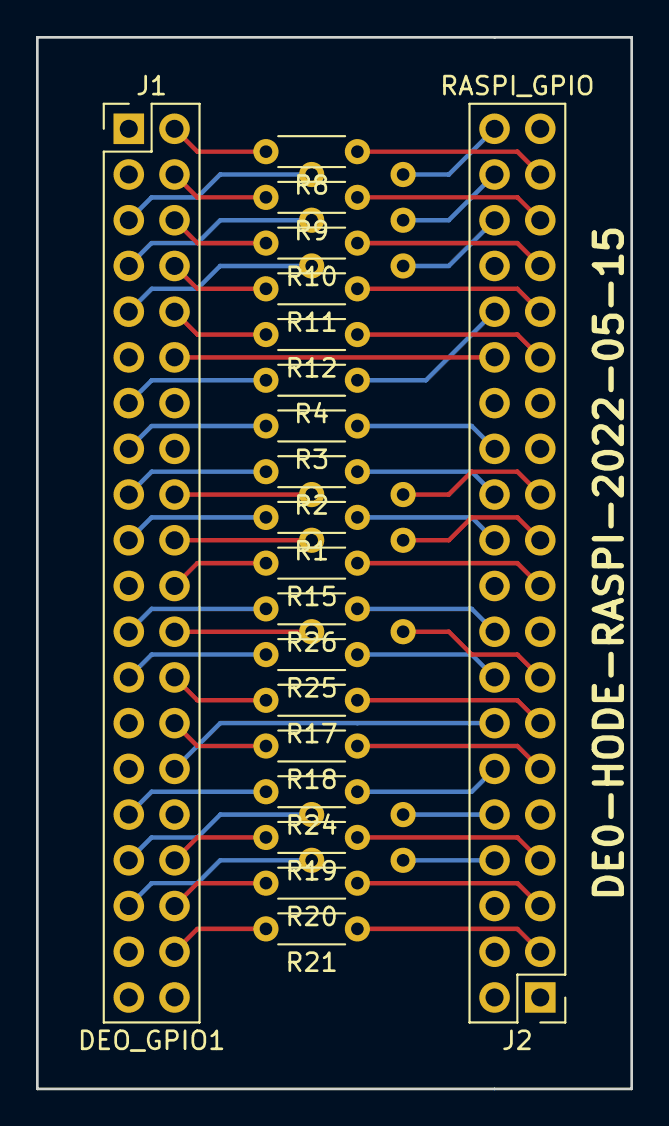
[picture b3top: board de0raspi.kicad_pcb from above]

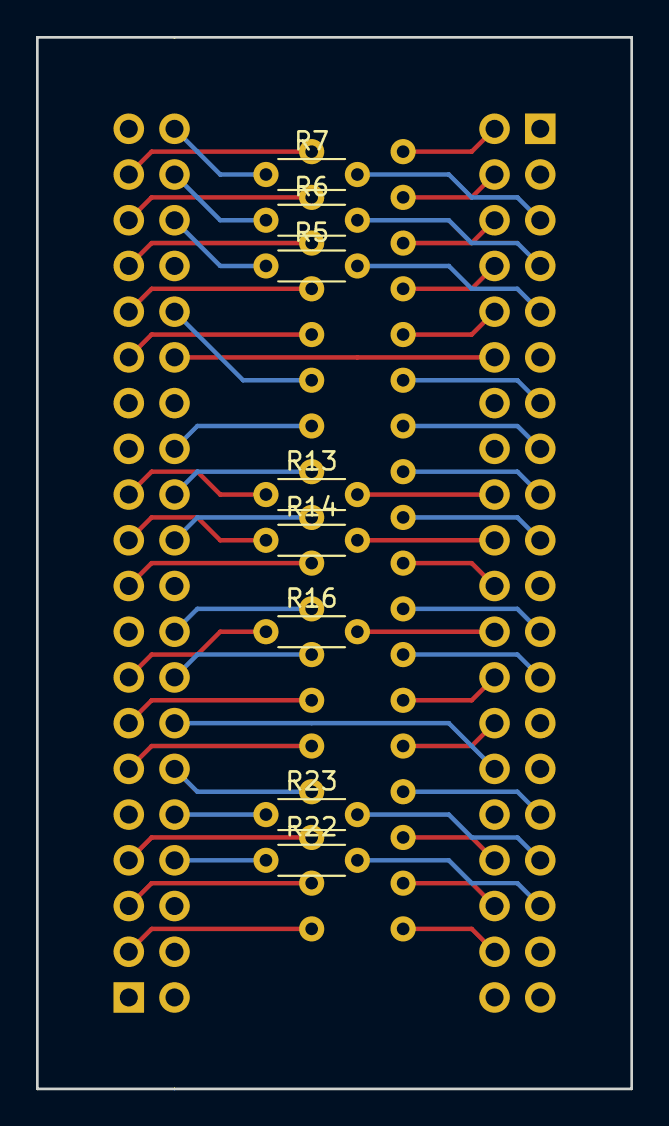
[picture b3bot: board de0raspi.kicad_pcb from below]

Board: 2 copper layers, 33.0 x 58.4 mm, 28 parts (8 on the bottom side), 54 nets.
